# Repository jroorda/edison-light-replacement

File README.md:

edison-light-replacement
========================

Design files and instructions for a replacement LED board for USB Edison bulbs.

All PCB files were created in Eagle version 7.0.0

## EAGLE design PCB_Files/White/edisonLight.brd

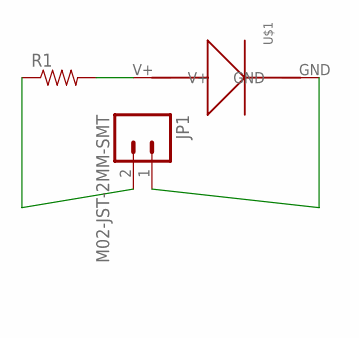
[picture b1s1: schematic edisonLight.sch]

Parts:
JP1: M02-JST-2MM-SMT; JST-2-SMD
R1: RESISTOR2010; R2010
U$1: MYLEDDEV; LTW-Z5630LED

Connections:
unnamed: R1.2, U$1.V+
unnamed: JP1.1 (2), U$1.GND
unnamed: JP1.2 (1), R1.1

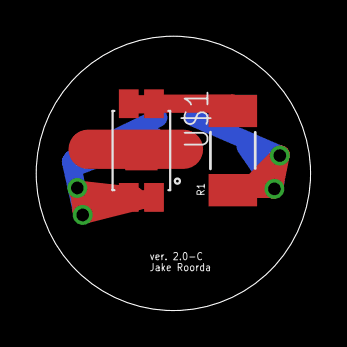
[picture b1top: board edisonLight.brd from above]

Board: 2 copper layers, 15.2 x 15.2 mm, 3 parts (1 on the bottom side), 3 nets.

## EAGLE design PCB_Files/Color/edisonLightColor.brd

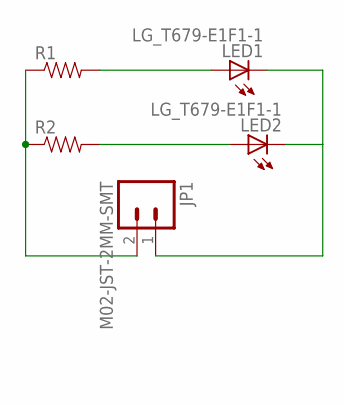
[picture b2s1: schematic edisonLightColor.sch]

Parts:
JP1: M02-JST-2MM-SMT; JST-2-SMD
LED1, LED2: LG_T679-E1F1-1; PLCC2
R1, R2: RESISTOR0805-RES; 0805

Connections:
unnamed: LED2.A, R2.2
unnamed: JP1.1 (2), LED1.C, LED2.C
unnamed: JP1.2 (1), R1.1, R2.1
unnamed: LED1.A, R1.2

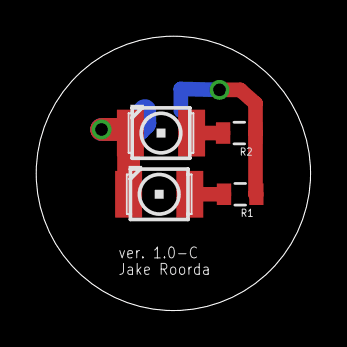
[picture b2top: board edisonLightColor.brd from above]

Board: 2 copper layers, 15.2 x 15.2 mm, 5 parts (1 on the bottom side), 4 nets.

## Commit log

2014-11-24 Updated License for hardware documentation
2014-11-24 Added PCB FIles
2014-11-24 Added Parts List
2014-12-07 Added PCB Assembly Pictures
2014-12-12 Completed Assembly Instructions

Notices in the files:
parts and their libraries:
SparkFun-Connectors: Licensing: Creative Commons ShareAlike 4.0 International - https://creativecommons.org/licenses/by-sa/4.0
